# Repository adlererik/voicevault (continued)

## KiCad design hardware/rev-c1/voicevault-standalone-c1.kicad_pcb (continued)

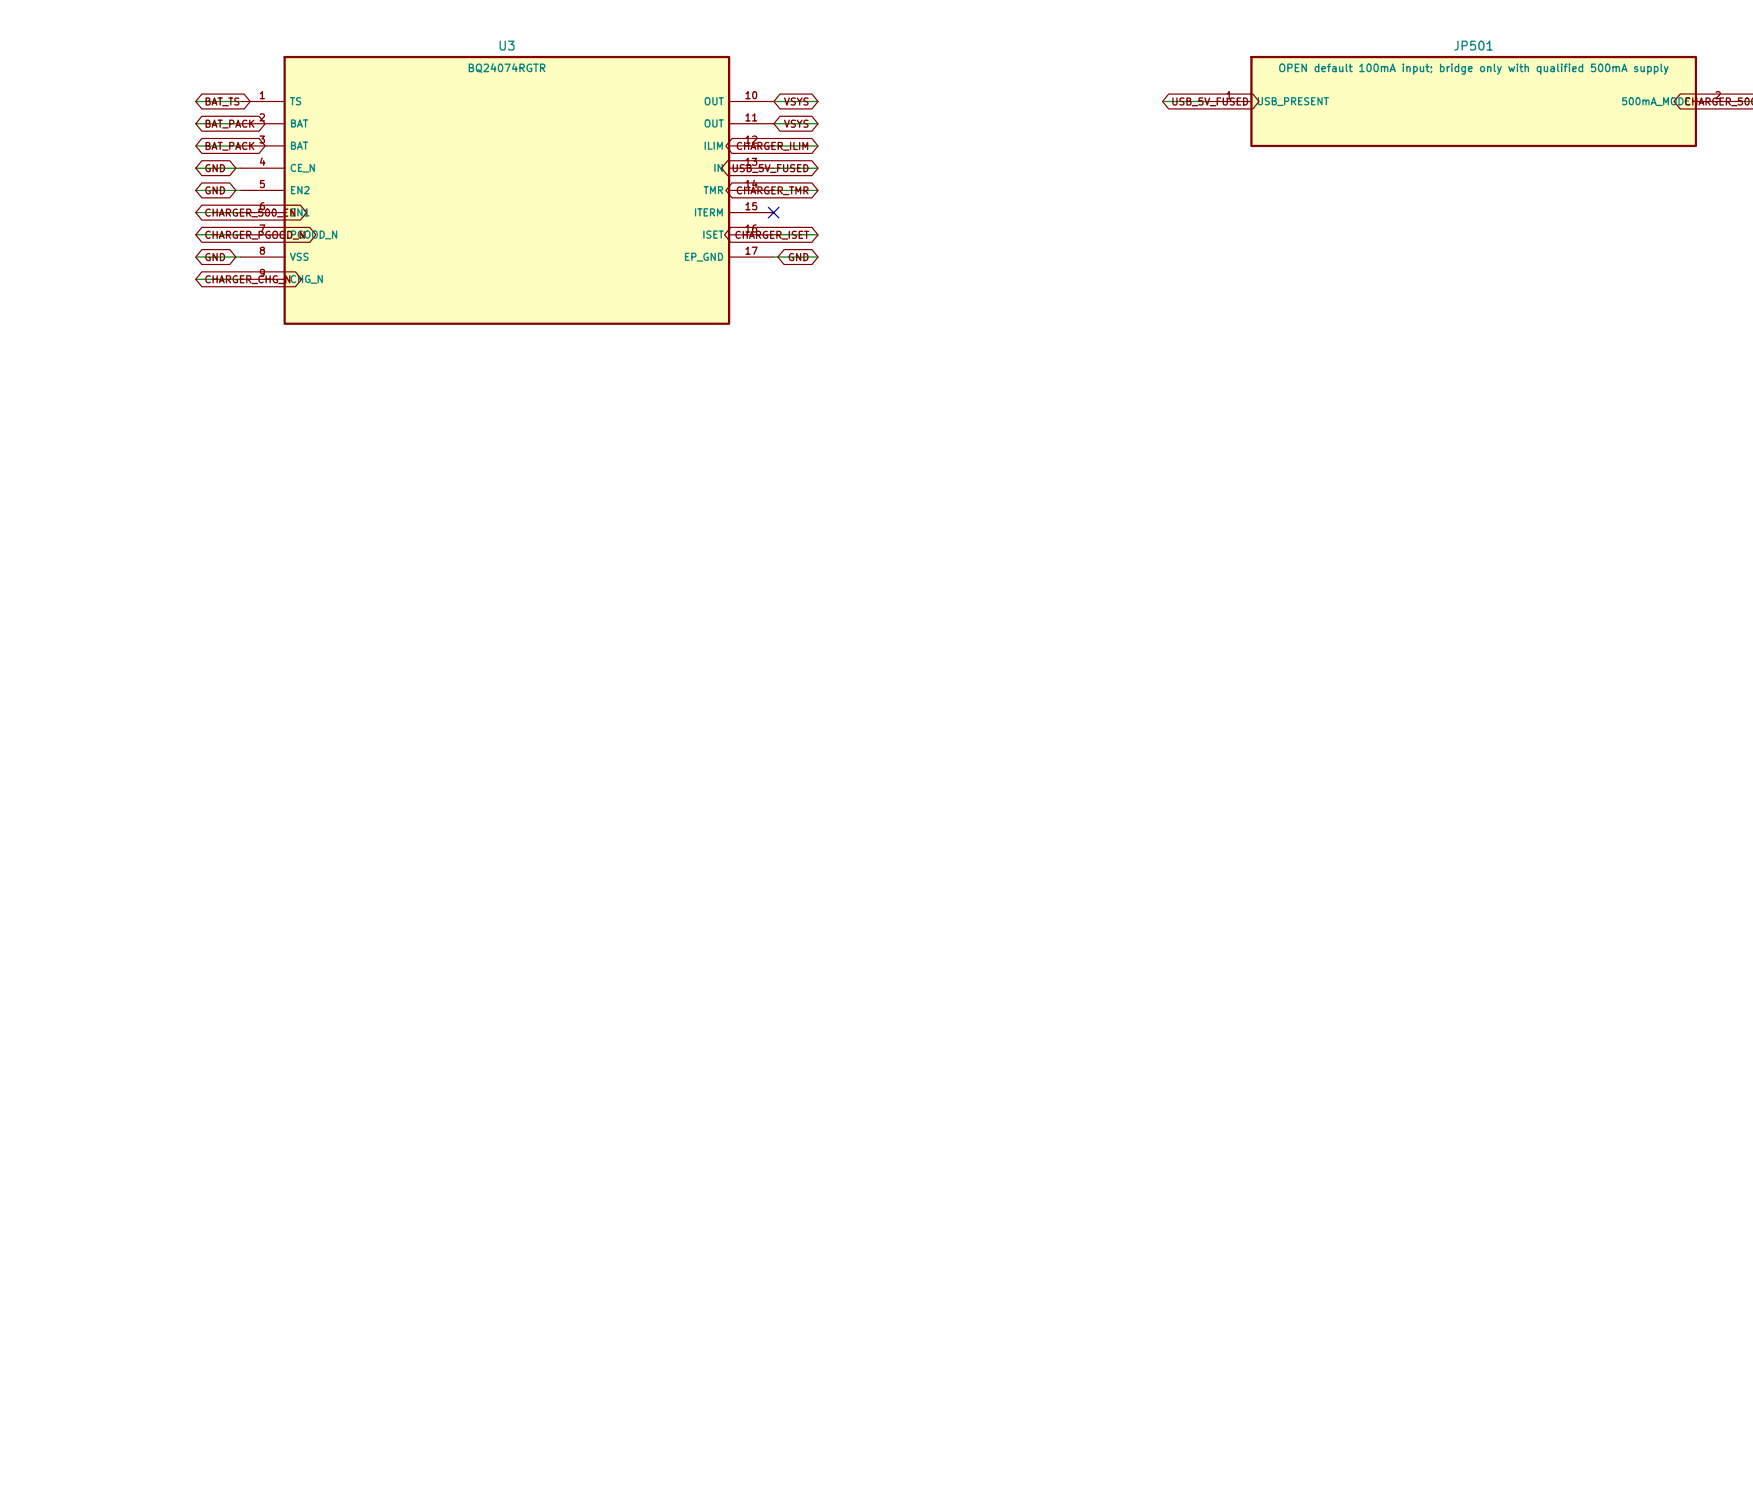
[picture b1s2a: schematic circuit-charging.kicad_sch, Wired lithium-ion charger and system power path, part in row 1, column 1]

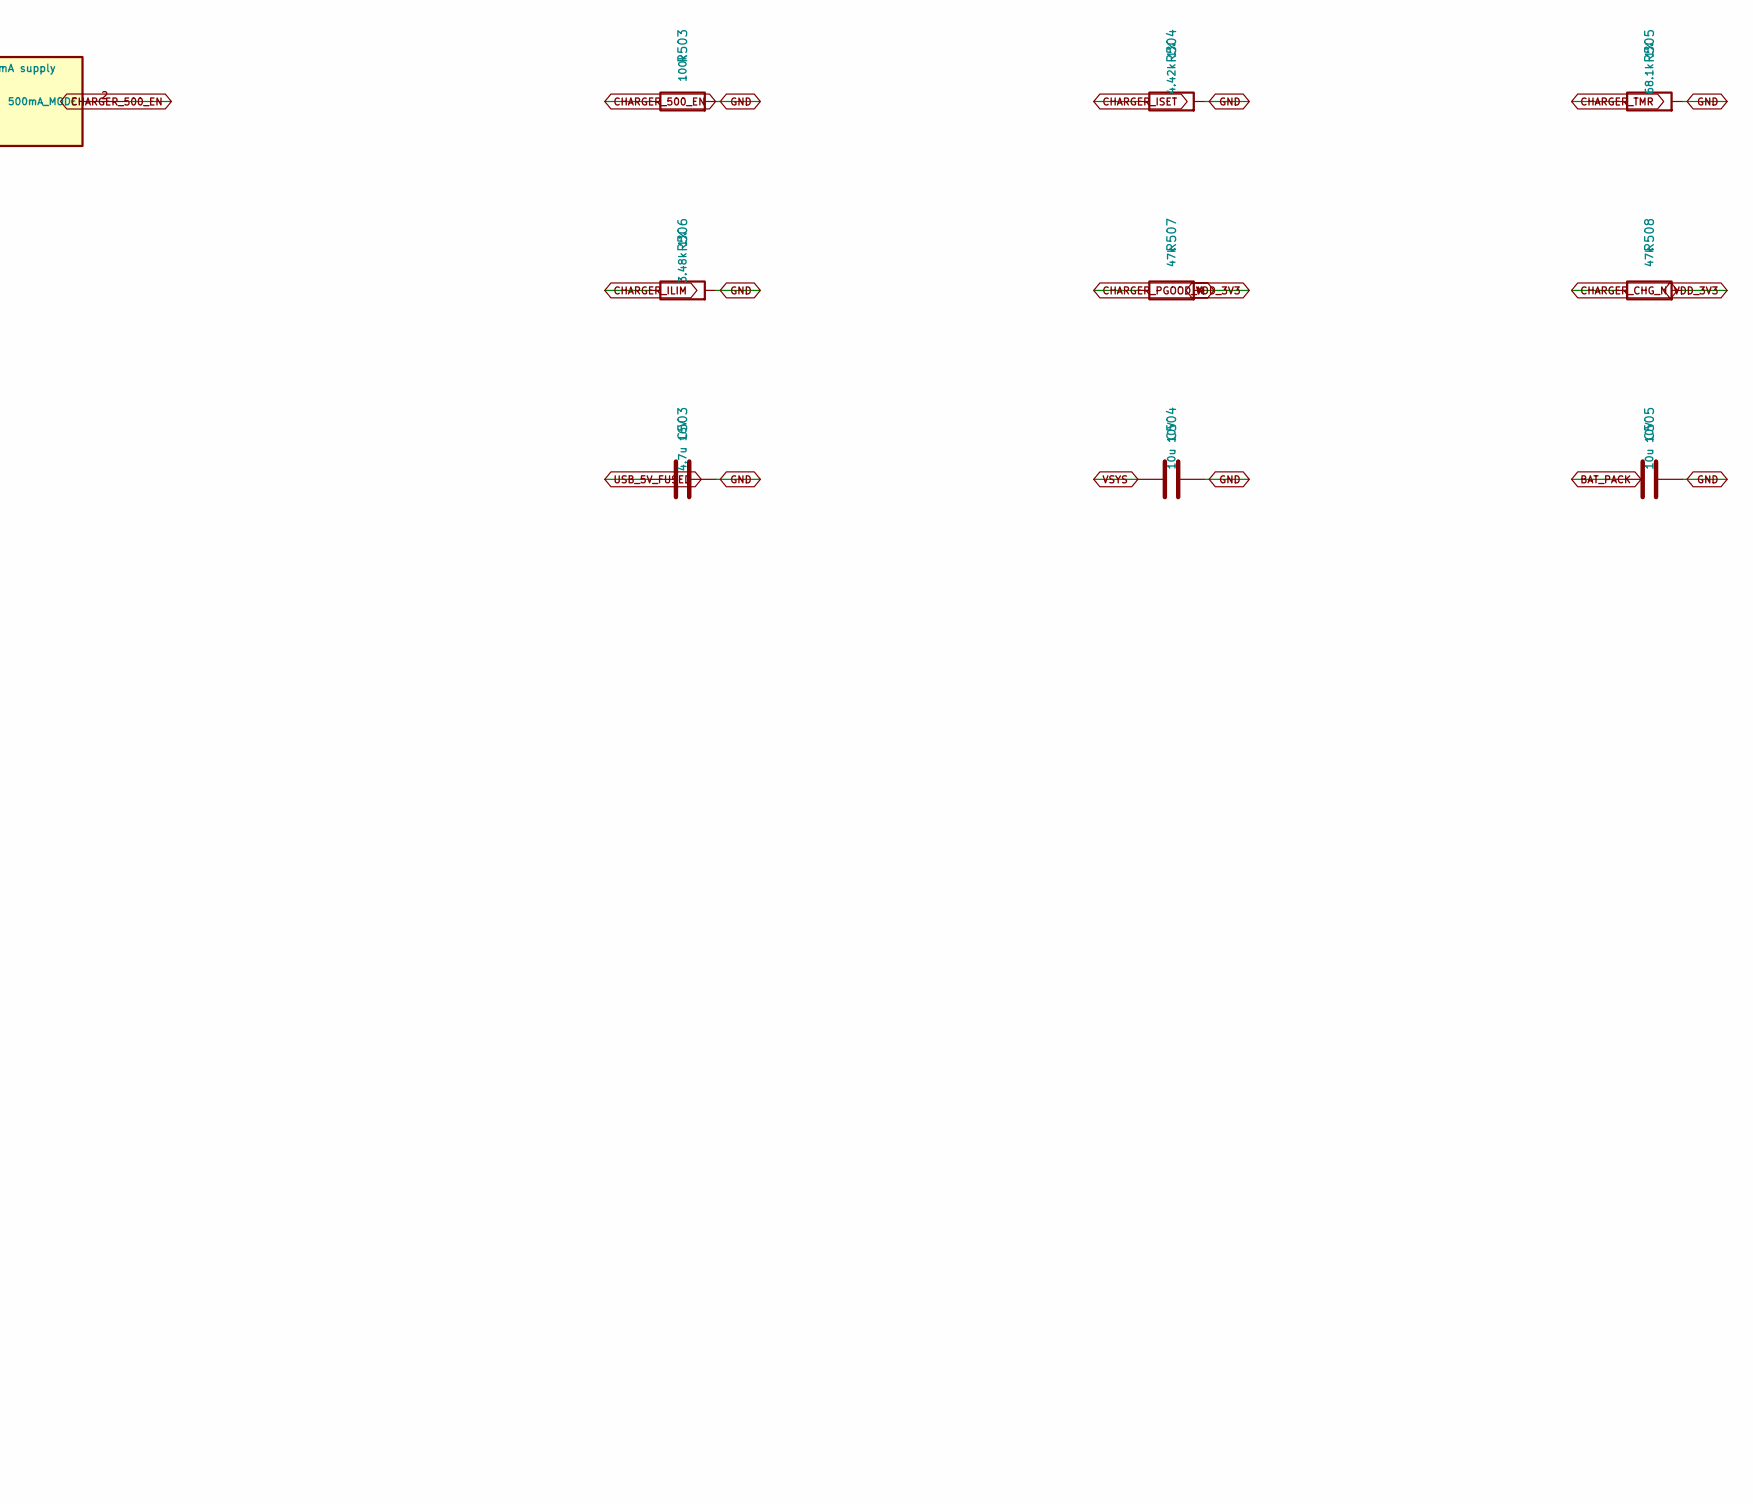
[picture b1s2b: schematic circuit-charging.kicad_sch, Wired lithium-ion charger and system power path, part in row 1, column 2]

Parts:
C503: 4.7u 16V; C_0603_1608Metric
C504, C505: 10u 10V; C_0603_1608Metric
JP501: OPEN default 100mA input; bridge only with qualif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; SolderJumper-2_P1.3mm_Open_RoundedPad1.0x1.5mm
R503: 100k; R_0402_1005Metric
R504: 4.42k 1%; R_0402_1005Metric
R505: 68.1k 1%; R_0402_1005Metric
R506: 3.48k 1%; R_0402_1005Metric
R507, R508: 47k; R_0402_1005Metric
U3: BQ24074RGTR; VQFN-16-1EP_3x3mm_P0.5mm_EP1.68x1.68mm

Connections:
BAT_PACK: C505.1, U3.2 (BAT), U3.3 (BAT); also elsewhere on the board
BAT_TS: U3.1 (TS); also elsewhere on the board
CHARGER_500_EN: JP501.2 (500mA_MODE), R503.1, U3.6 (EN1)
CHARGER_CHG_N: R508.1, U3.9 (CHG_N); also elsewhere on the board
CHARGER_ILIM: R506.1, U3.12 (ILIM)
CHARGER_ISET: R504.1, U3.16 (ISET)
CHARGER_PGOOD_N: R507.1, U3.7 (PGOOD_N); also elsewhere on the board
CHARGER_TMR: R505.1, U3.14 (TMR)
GND: C503.2, C504.2, C505.2, R503.2, R504.2, R505.2, R506.2, U3.4 (CE_N), U3.5 (EN2), U3.8 (VSS), U3.17 (EP_GND); also elsewhere on the board
USB_5V_FUSED: C503.1, JP501.1 (USB_PRESENT), U3.13 (IN); also elsewhere on the board
VDD_3V3: R507.2, R508.2; also elsewhere on the board
VSYS: C504.1, U3.10 (OUT), U3.11 (OUT); also elsewhere on the board

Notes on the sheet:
BQ24074: TS=10k pack NTC; CE low; timer active; ITERM open selects default.
ISET 4.42k: approximately 201mA target, subject to actual pack acceptance.
JP501 open selects 100mA source limit. Bridge only for an appropriate 5V source; no USB data enumeration.
Input/system and battery paths need real charger/pack qualification; no complete charger SPICE model asserted.

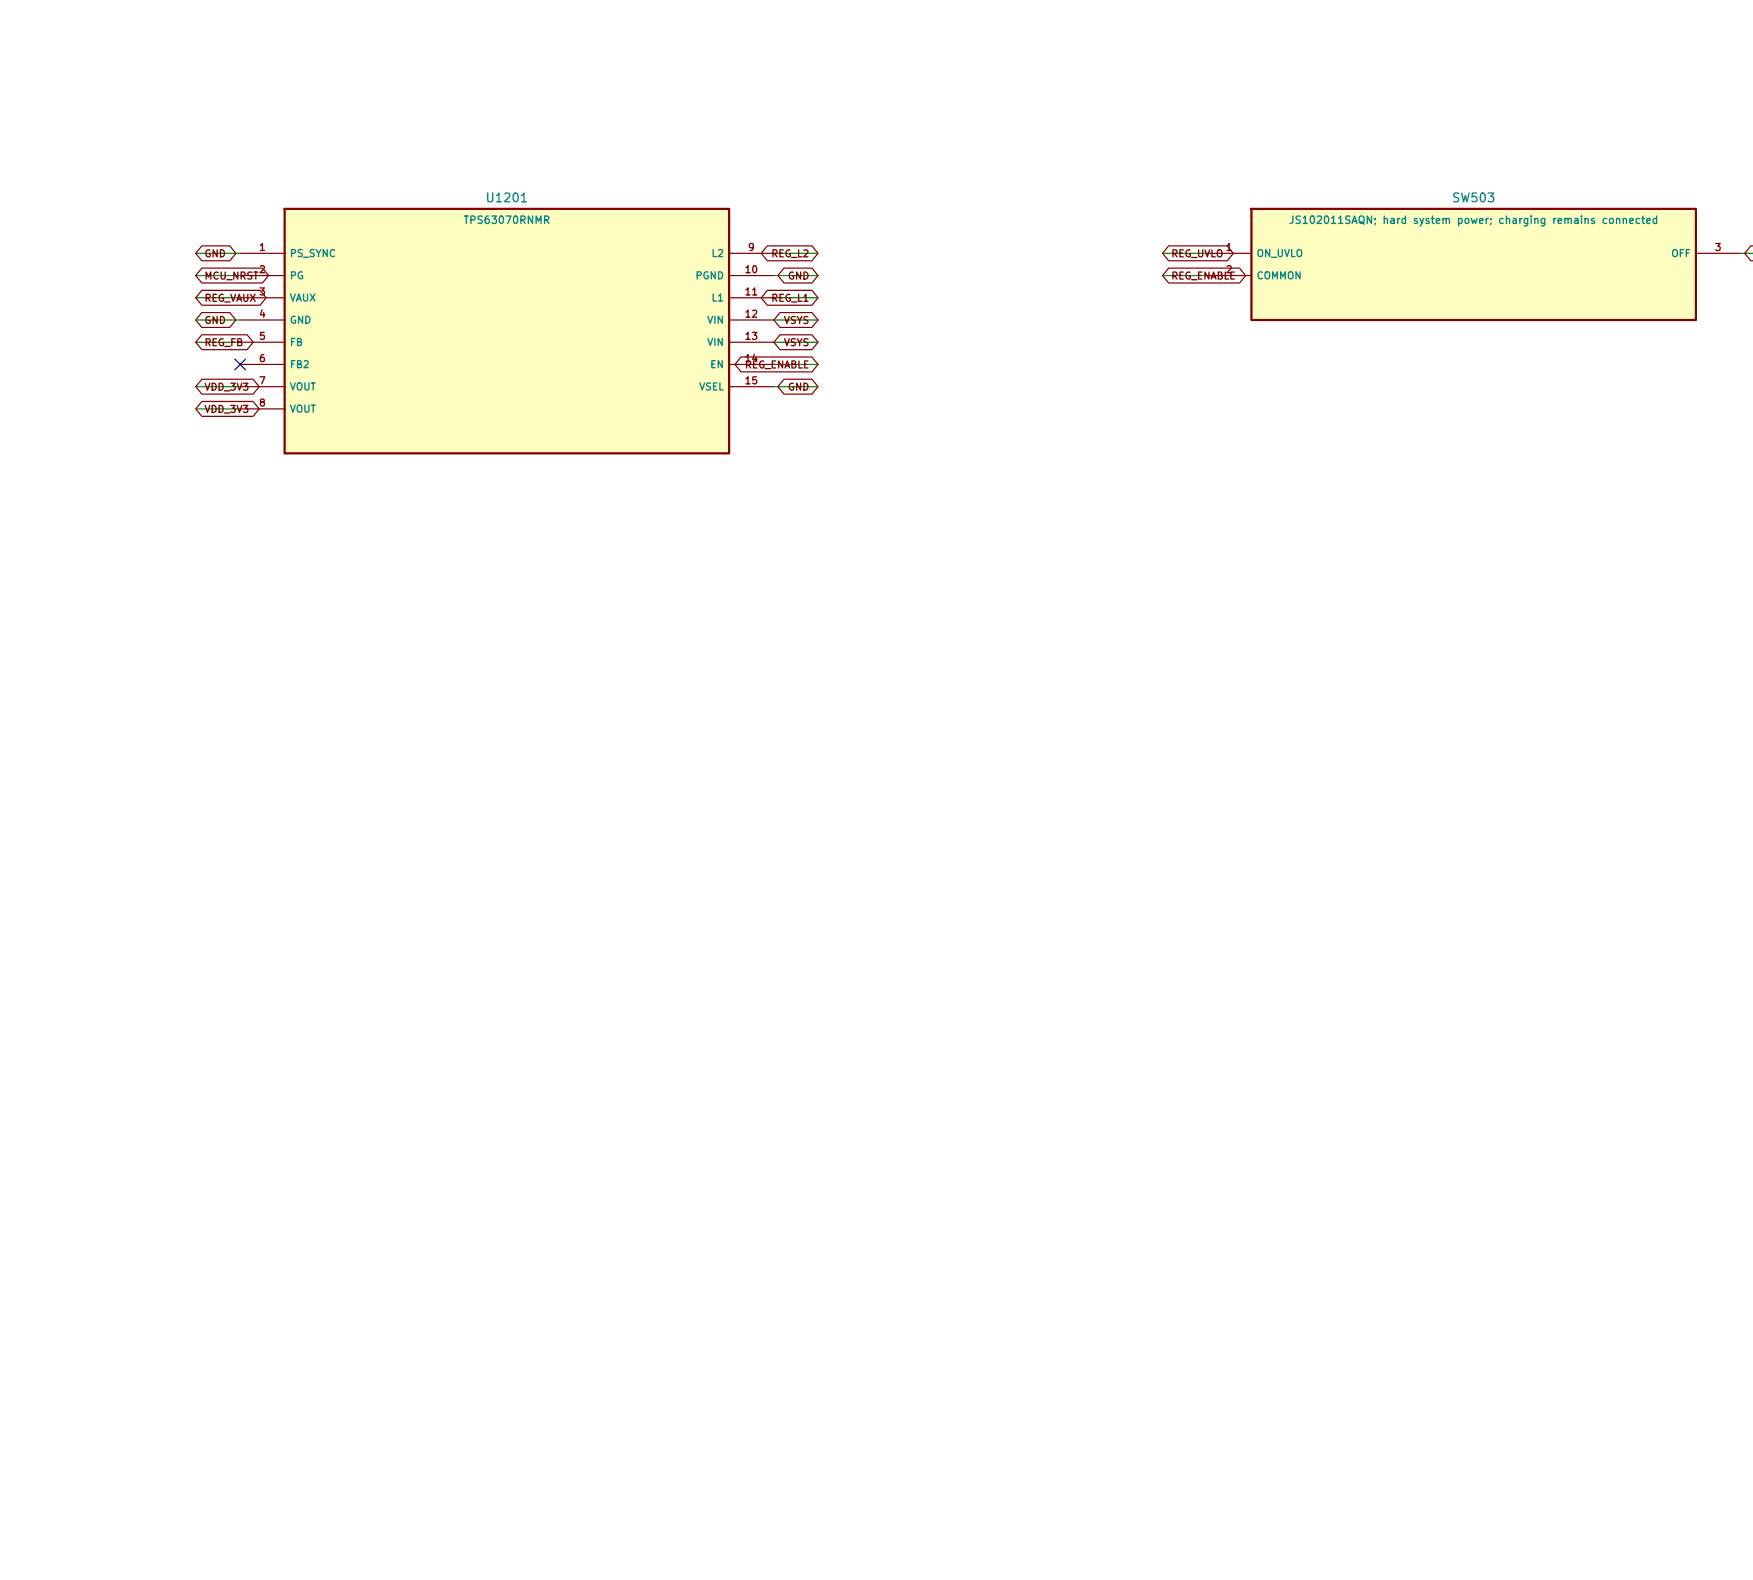
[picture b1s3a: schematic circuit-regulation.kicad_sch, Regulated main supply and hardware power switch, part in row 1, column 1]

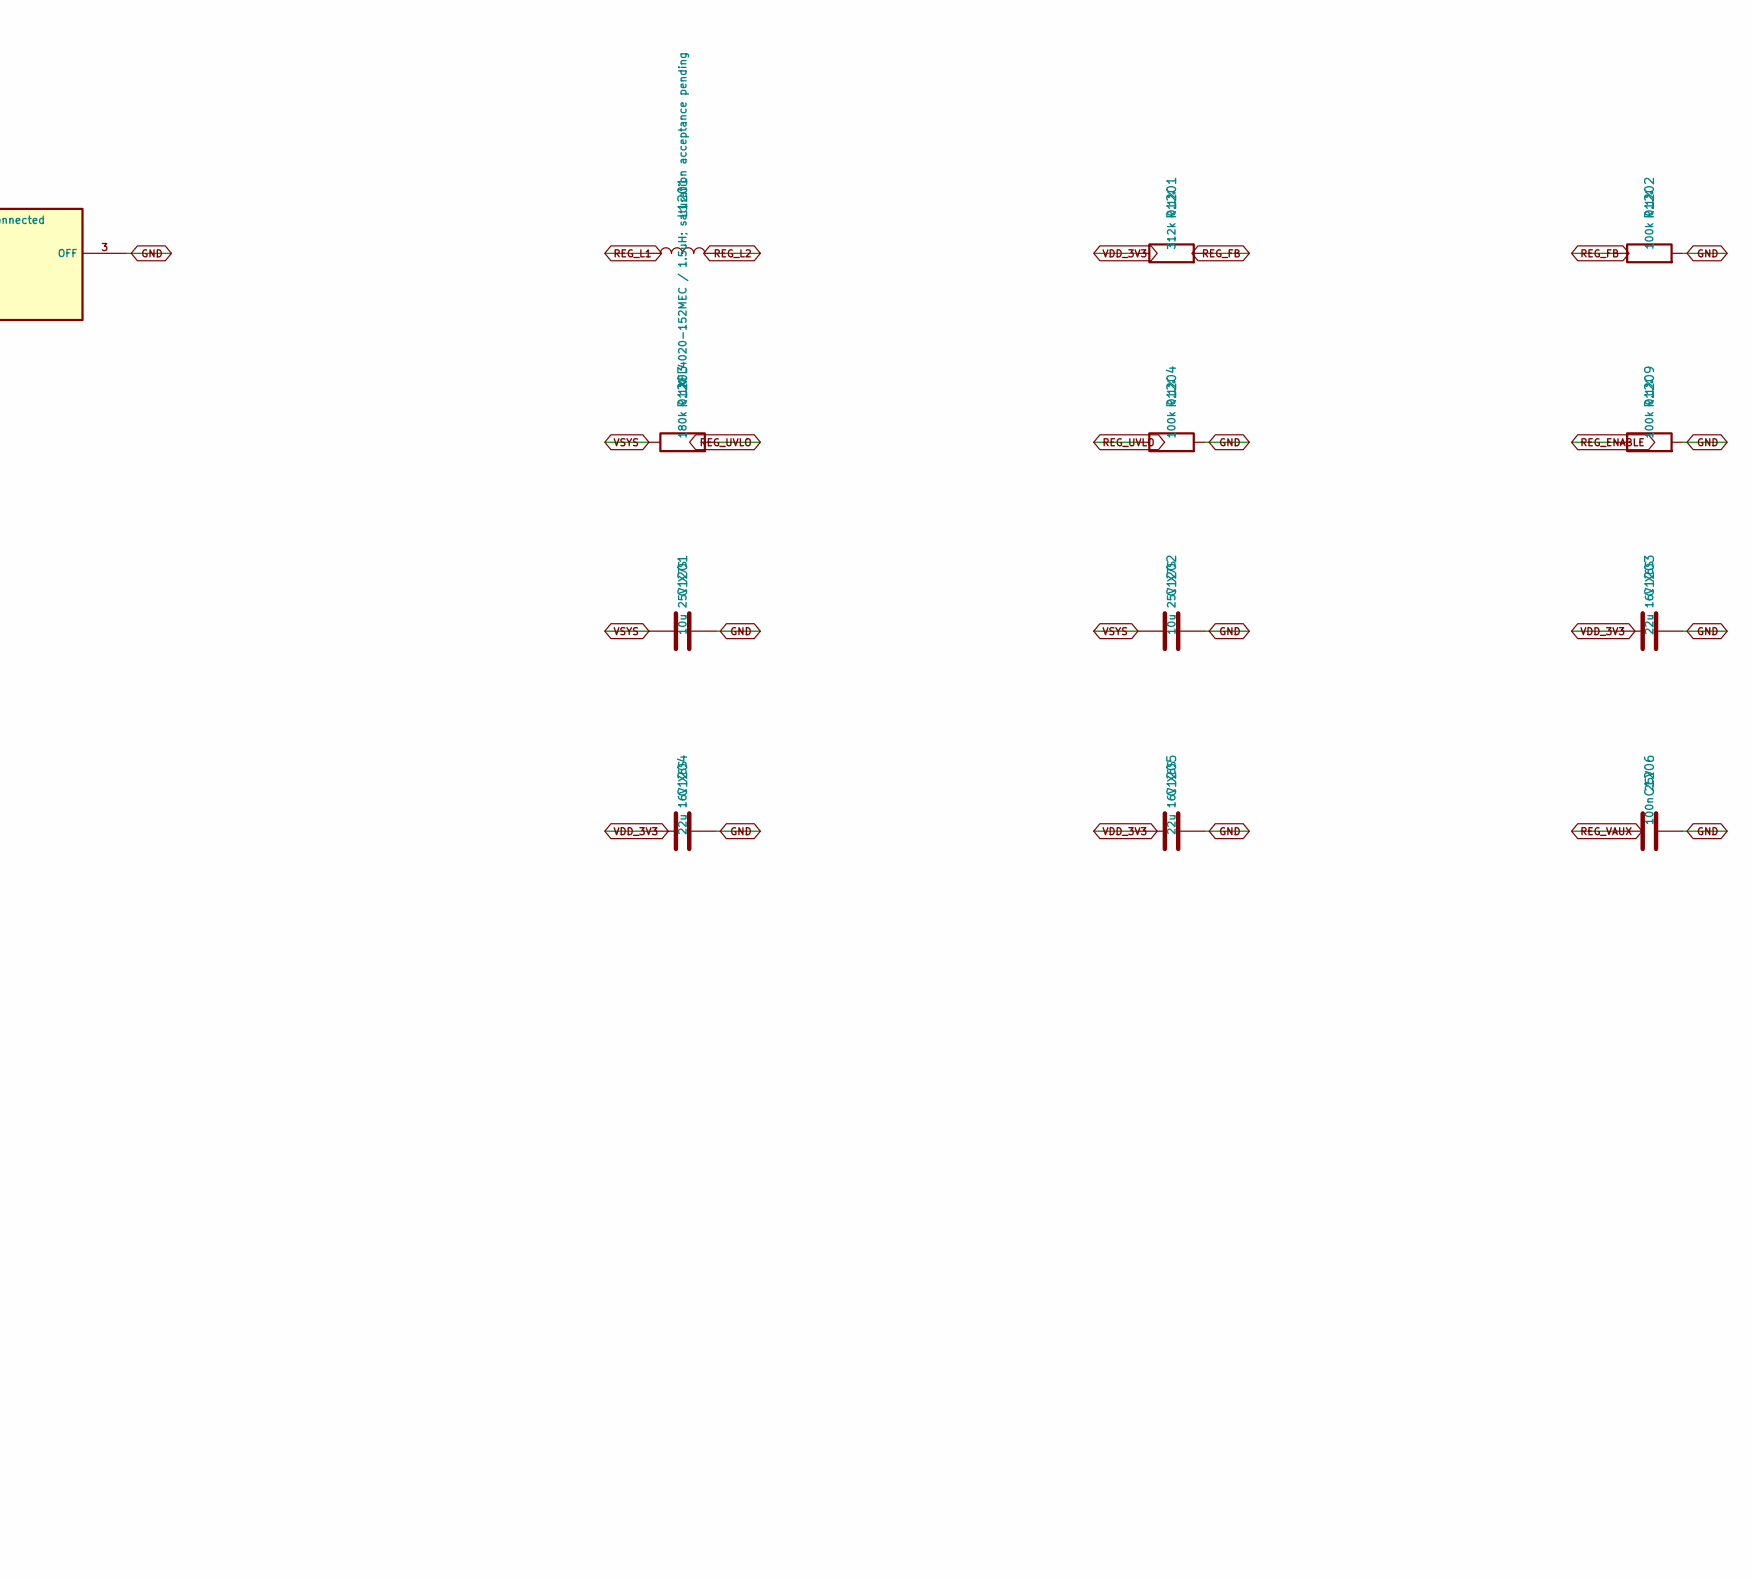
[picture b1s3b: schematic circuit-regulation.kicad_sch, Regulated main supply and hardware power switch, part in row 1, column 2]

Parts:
C1201, C1202: 10u 25V X7S; C_0805_2012Metric
C1203, C1204, C1205: 22u 16V X6S; C_0805_2012Metric
C1206: 100n 25V; C_0603_1608Metric
L1201: XFL4020-152MEC / 1.5uH; saturation acceptance pen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; Coilcraft_XFL4020
R1201: 312k 0.1%; R_0402_1005Metric
R1202, R1204, R1209: 100k 0.1%; R_0402_1005Metric
R1203: 180k 0.1%; R_0402_1005Metric
SW503: JS102011SAQN; hard system power; charging remains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; SW_SPDT_CK_JS102011SAQN
U1201: TPS63070RNMR; TPS63070_RNM0015A

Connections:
GND: C1201.2, C1202.2, C1203.2, C1204.2, C1205.2, C1206.2, R1202.2, R1204.2, R1209.2, SW503.3 (OFF), U1201.1 (PS_SYNC), U1201.4 (GND), U1201.10 (PGND), U1201.15 (VSEL); also elsewhere on the board
MCU_NRST: U1201.2 (PG); also elsewhere on the board
REG_ENABLE: R1209.1, SW503.2 (COMMON), U1201.14 (EN); also elsewhere on the board
REG_FB: R1201.2, R1202.1, U1201.5 (FB)
REG_L1: L1201.1, U1201.11 (L1)
REG_L2: L1201.2, U1201.9 (L2)
REG_UVLO: R1203.2, R1204.1, SW503.1 (ON_UVLO)
REG_VAUX: C1206.1, U1201.3 (VAUX)
VDD_3V3: C1203.1, C1204.1, C1205.1, R1201.1, U1201.7 (VOUT), U1201.8 (VOUT); also elsewhere on the board
VSYS: C1201.1, C1202.1, R1203.1, U1201.12 (VIN), U1201.13 (VIN); also elsewhere on the board

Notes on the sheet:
Forced PWM; nominal main output 0.8*(1+312k/100k)=3.296V. PG is open drain on shared reset.
ON: 180k/(100k || 100k) EN divider; nominal rising 3.68V / falling 3.22V. EN also defined during switch transition.
Electrical inventory is unplaced. Quilter must preserve short power loops and return paths.
Manufacturer converter model omits temperature and operating/shutdown current; bench gates remain.

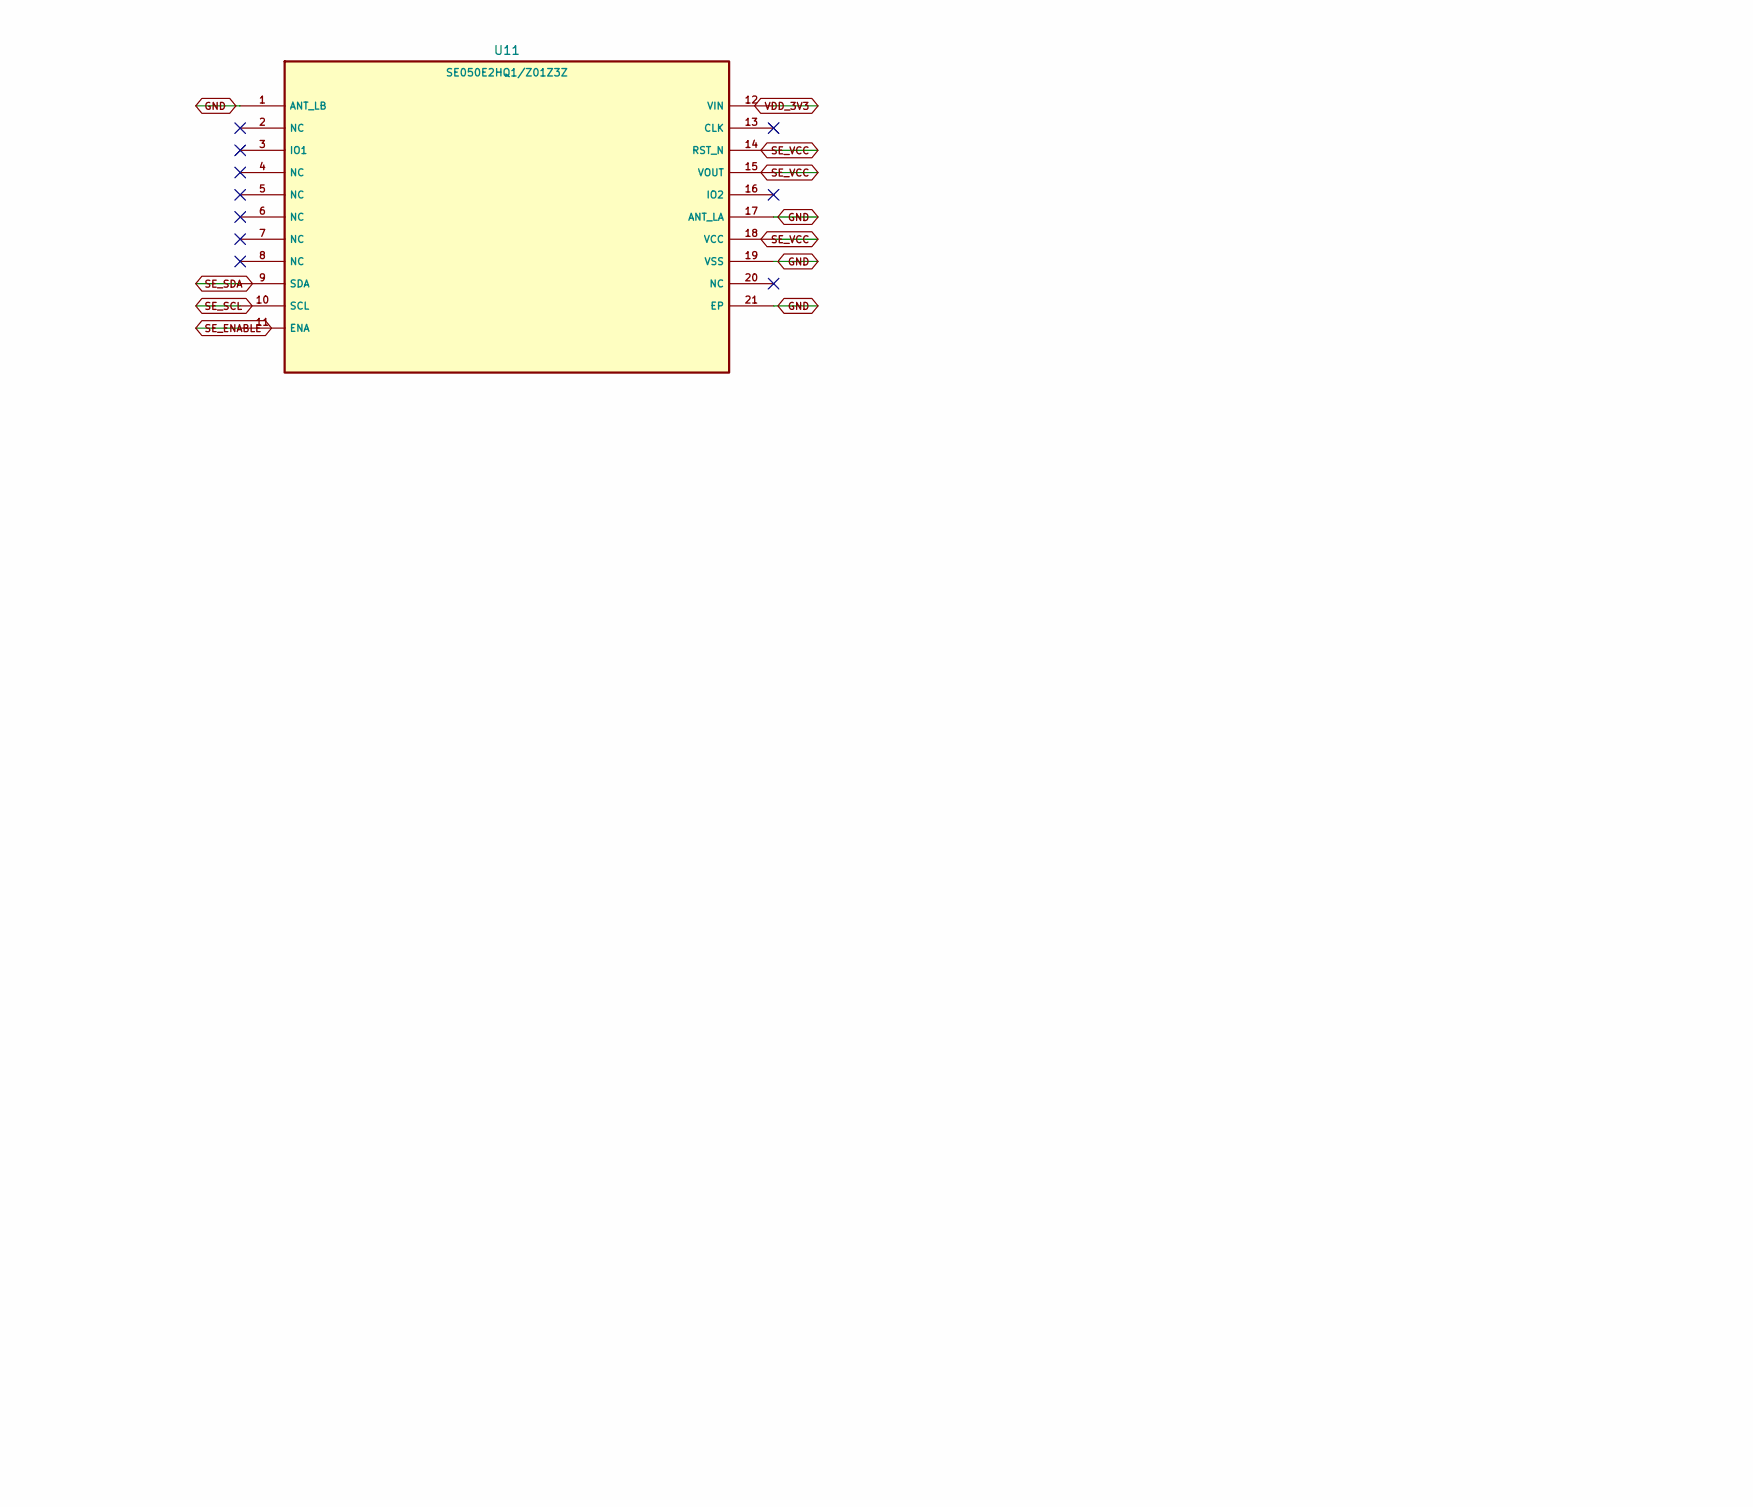
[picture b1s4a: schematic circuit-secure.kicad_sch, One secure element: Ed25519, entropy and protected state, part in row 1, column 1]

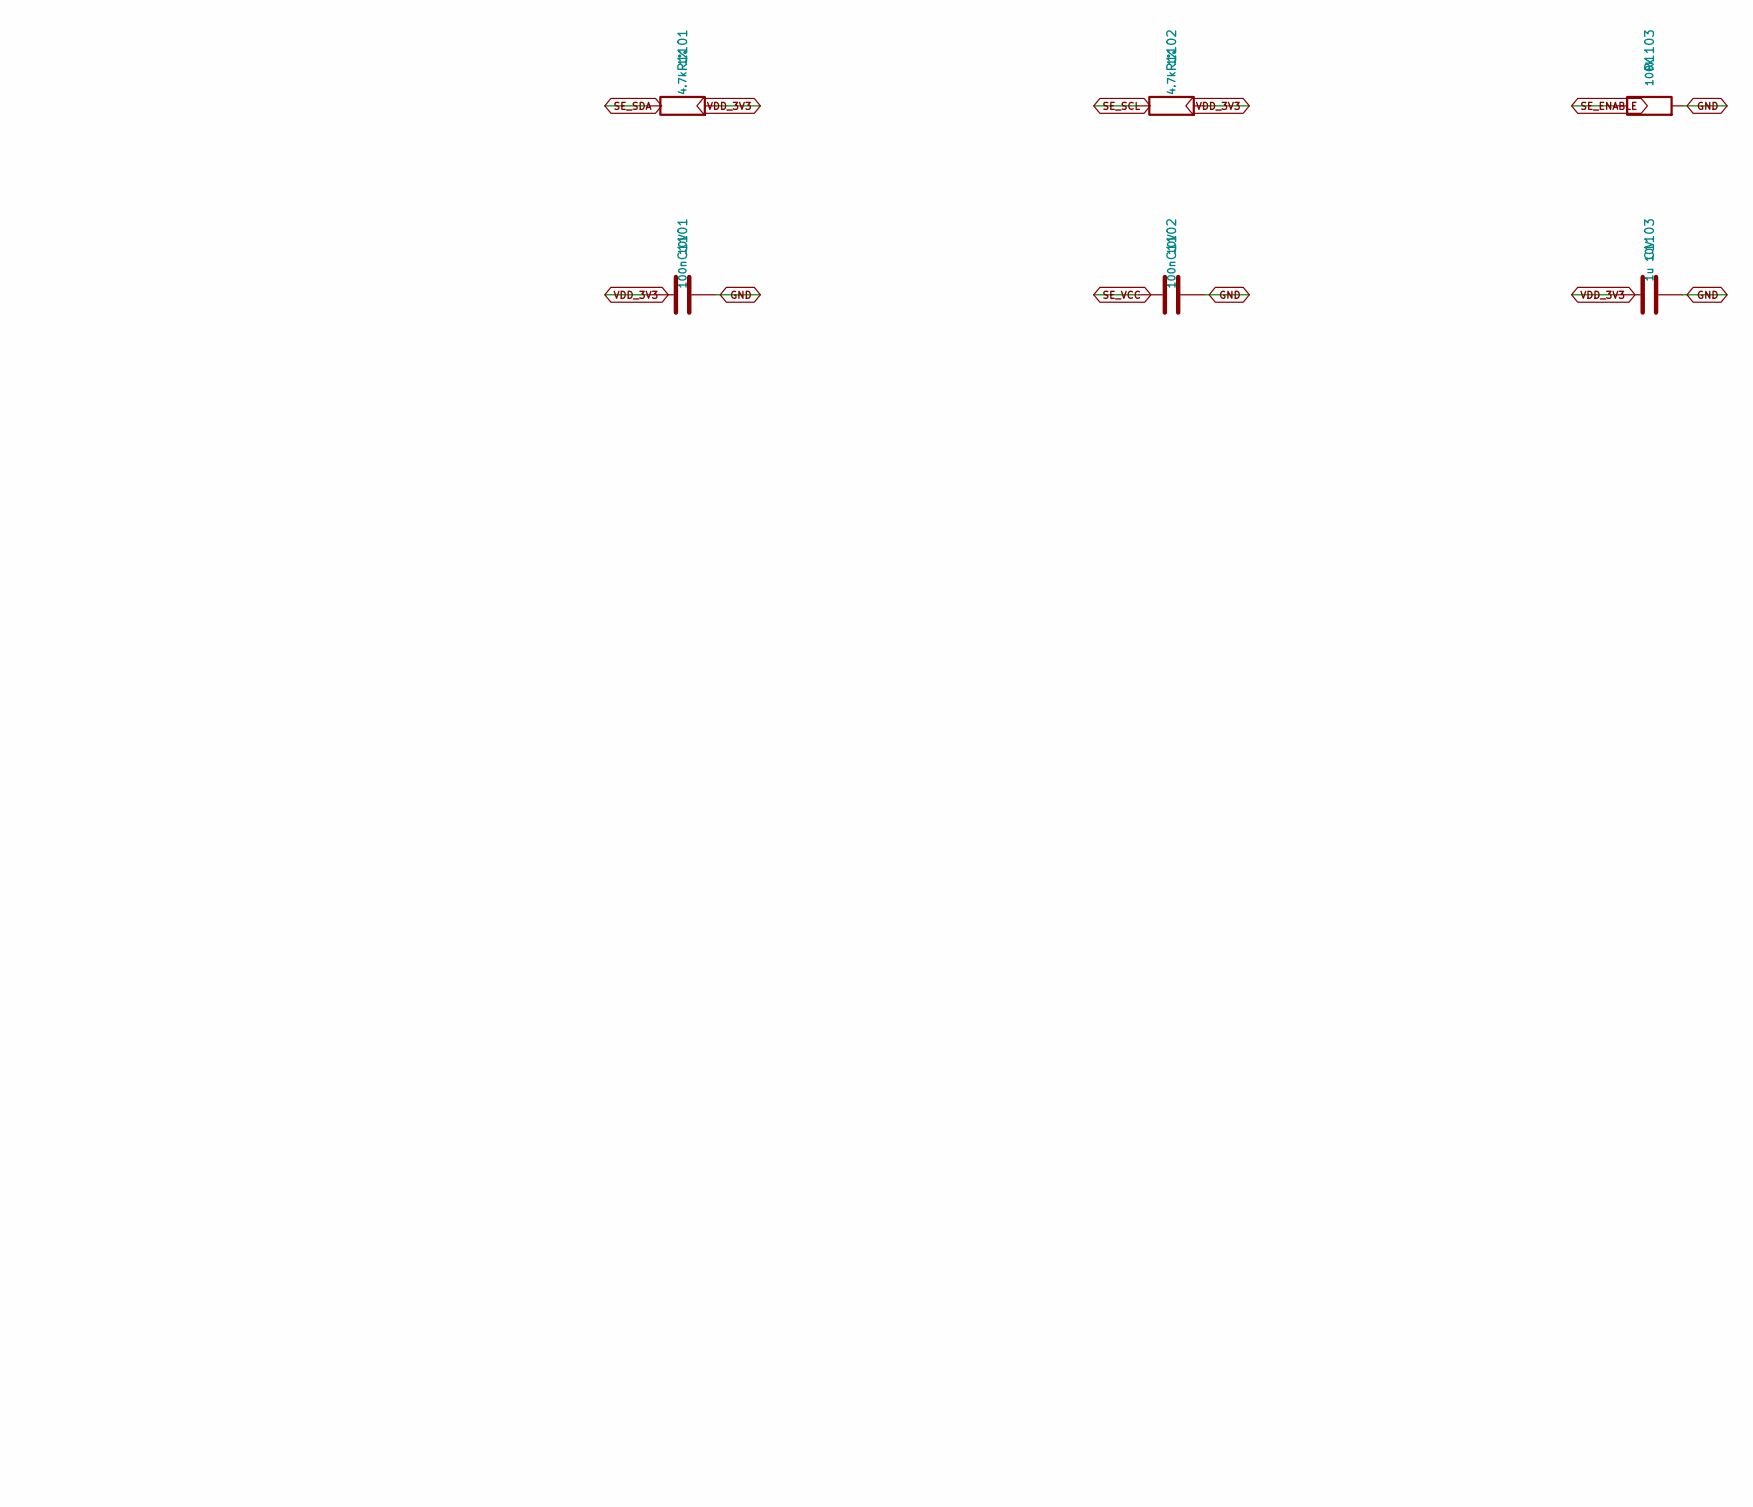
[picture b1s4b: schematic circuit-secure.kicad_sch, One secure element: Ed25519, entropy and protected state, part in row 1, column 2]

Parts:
C1101, C1102: 100n 10V; C_0603_1608Metric
C1103: 1u 10V; C_0603_1608Metric
R1101, R1102: 4.7k 1%; R_0402_1005Metric
R1103: 100k; R_0402_1005Metric
U11: SE050E2HQ1/Z01Z3Z; NXP_SOT1969-1

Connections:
GND: C1101.2, C1102.2, C1103.2, R1103.2, U11.1 (ANT_LB), U11.17 (ANT_LA), U11.19 (VSS), U11.21 (EP); also elsewhere on the board
SE_ENABLE: R1103.1, U11.11 (ENA); also elsewhere on the board
SE_SCL: R1102.1, U11.10 (SCL); also elsewhere on the board
SE_SDA: R1101.1, U11.9 (SDA); also elsewhere on the board
SE_VCC: C1102.1, U11.14 (RST_N), U11.15 (VOUT), U11.18 (VCC); also elsewhere on the board
VDD_3V3: C1101.1, C1103.1, R1101.2, R1102.2, U11.12 (VIN); also elsewhere on the board

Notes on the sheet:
NXP E variant only. Unused antenna pins grounded. VOUT connects to VCC for deep power-down.
MCU PD12/PD13 use I2C4 at initial 100kHz; 4.7k pull-ups require sink/rise-time check.
ENA defaults low; firmware must initialize/provision a protected channel before key/entropy use.
Private-key, counter, durable-storage and real RNG behavior require chip-backed tests; no silicon simulation claimed.
